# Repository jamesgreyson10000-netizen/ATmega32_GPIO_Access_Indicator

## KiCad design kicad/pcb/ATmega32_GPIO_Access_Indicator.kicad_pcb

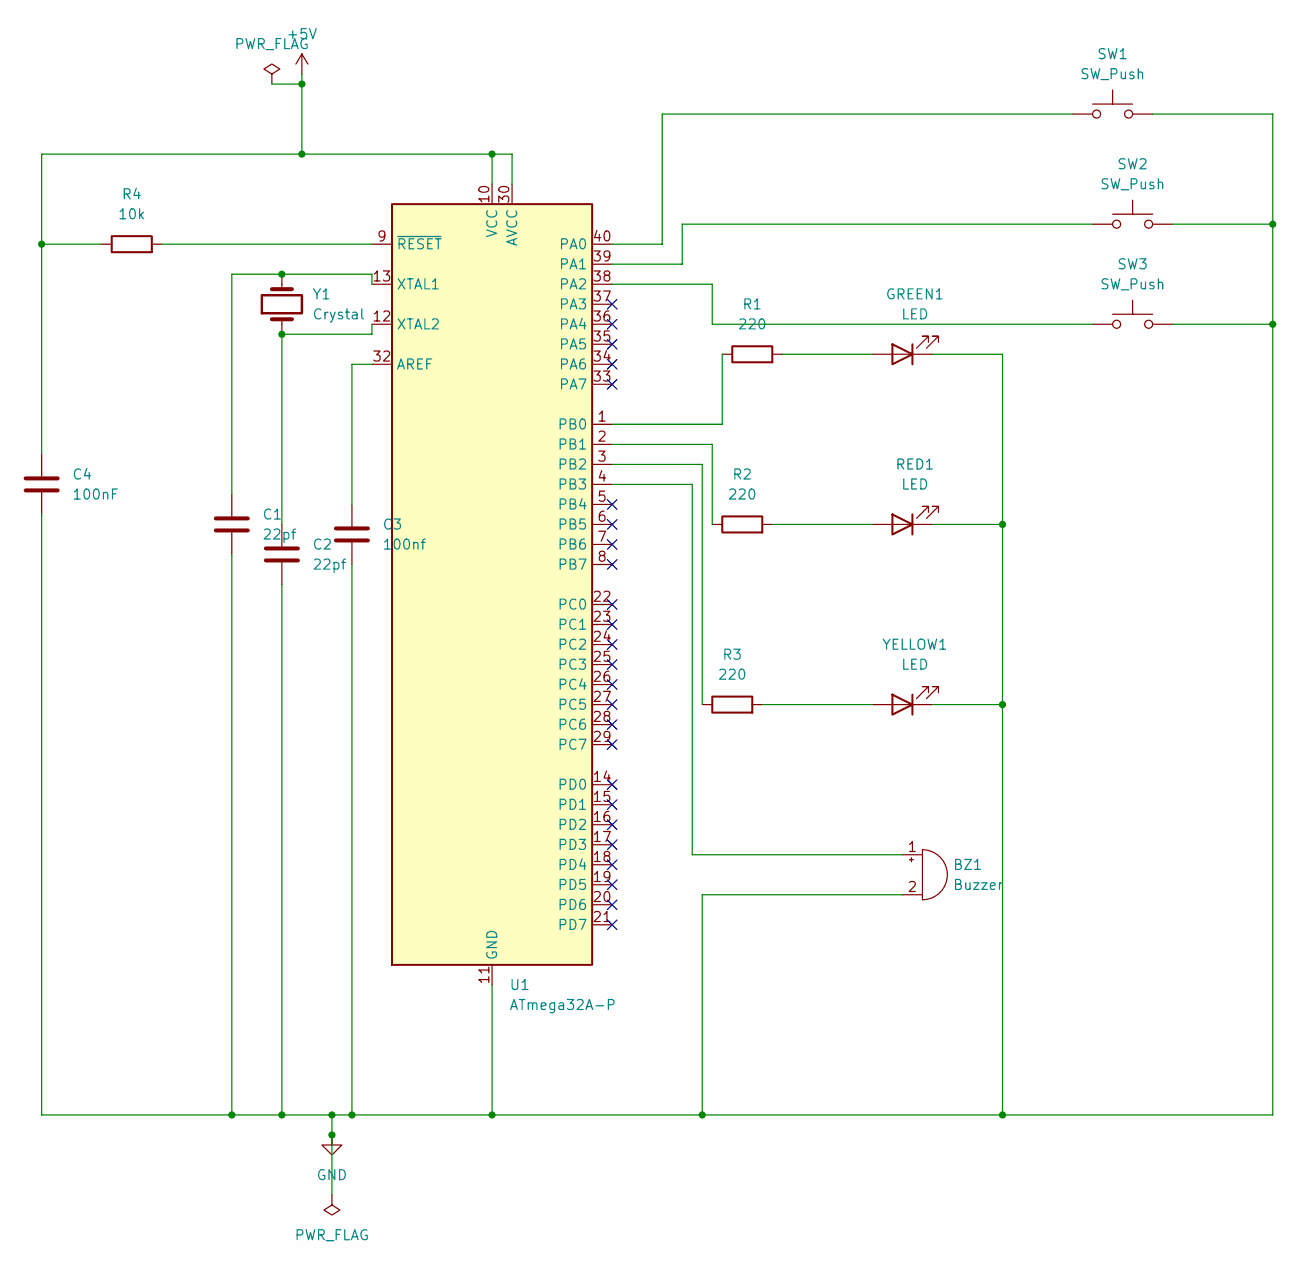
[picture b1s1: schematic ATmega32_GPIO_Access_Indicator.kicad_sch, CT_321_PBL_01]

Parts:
BZ1: Buzzer; Buzzer_12x9.5RM7.6
C1, C2: 22pf; C_Disc_D5.0mm_W2.5mm_P5.00mm
C3: 100nf; C_Disc_D5.0mm_W2.5mm_P5.00mm
C4: 100nF; C_Disc_D5.0mm_W2.5mm_P5.00mm
GREEN1: LED; LED_D5.0mm
R1, R2, R3: 220; R_Axial_DIN0207_L6.3mm_D2.5mm_P7.62mm_Horizontal
R4: 10k; R_Axial_DIN0207_L6.3mm_D2.5mm_P7.62mm_Horizontal
RED1: LED; LED_D5.0mm
SW1, SW2, SW3: SW_Push; SW_PUSH_6mm
U1: ATmega32A-P; DIP-40_W15.24mm
Y1: Crystal; Crystal_HC49-U_Vertical
YELLOW1: LED; LED_D5.0mm

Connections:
+5V: C4.1, R4.1, U1.10 (VCC), U1.30 (AVCC)
GND: BZ1.2 (-), C1.2, C2.2, C3.2, C4.2, GREEN1.1 (K), RED1.1 (K), SW1.2, SW2.2, SW3.2, U1.11 (GND), U1.31 (GND), YELLOW1.1 (K)
unnamed: BZ1.1 (+), U1.4 (PB3)
unnamed: GREEN1.2 (A), R1.2
unnamed: R2.2, RED1.2 (A)
unnamed: C3.1, U1.32 (AREF)
unnamed: SW1.1, U1.40 (PA0)
unnamed: SW2.1, U1.39 (PA1)
unnamed: SW3.1, U1.38 (PA2)
unnamed: R1.1, U1.1 (PB0)
unnamed: R2.1, U1.2 (PB1)
unnamed: R3.1, U1.3 (PB2)
unnamed: C1.1, U1.13 (XTAL1), Y1.2
unnamed: C2.1, U1.12 (XTAL2), Y1.1
unnamed: R4.2, U1.9 (~RESET)
unnamed: R3.2, YELLOW1.2 (A)

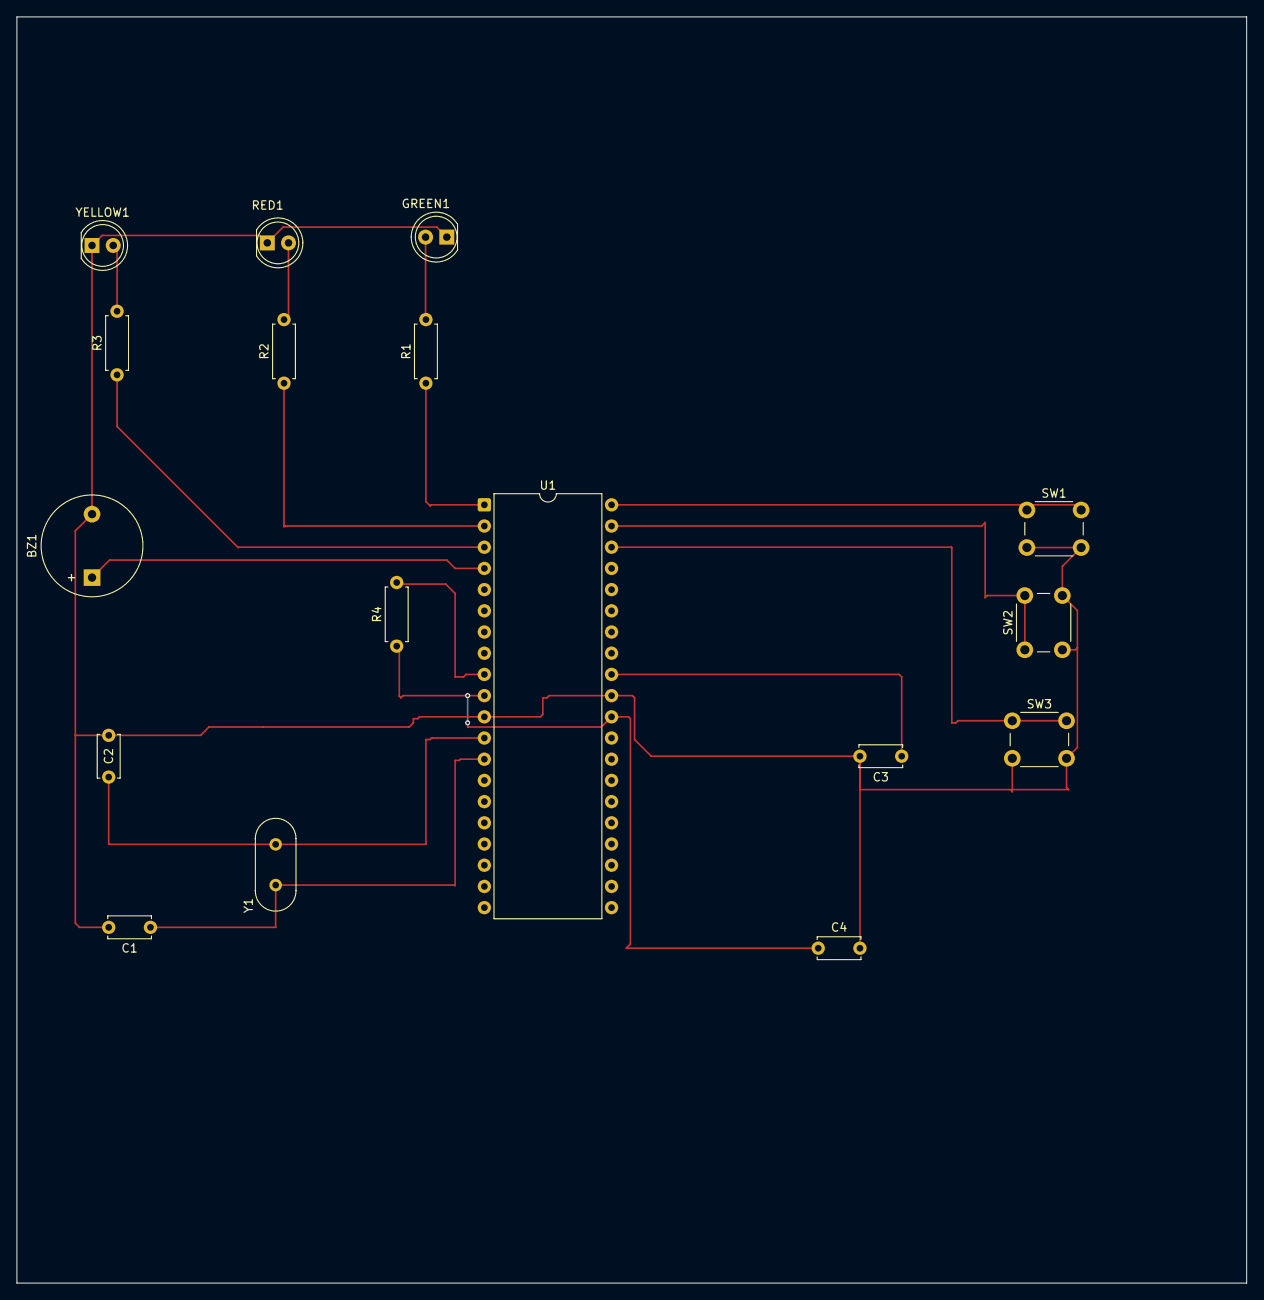
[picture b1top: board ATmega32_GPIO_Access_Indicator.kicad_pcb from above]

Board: 2 copper layers, 147.3 x 151.7 mm, 17 parts (0 on the bottom side), 16 nets.

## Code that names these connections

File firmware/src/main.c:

#define F_CPU 16000000UL
#include <avr/io.h>
#include <util/delay.h>

/* ── Pin aliases ─────────────────────────────── */
#define BTN_OK      PA0   /* Correct access button */
#define BTN_WRONG   PA1   /* Wrong access button   */
#define BTN_RESET   PA2   /* Reset button          */

#define LED_GREEN   PB0
#define LED_RED     PB1
#define LED_YELLOW  PB2
#define BUZZER      PB3

/* ── Helper macros ───────────────────────────── */
#define BTN_PRESSED(pin)   ( !(PINA & (1 << (pin))) )
#define BTN_RELEASED(pin)  (   PINA & (1 << (pin))  )

int main(void)
{
    /* PORTA = all inputs */
    DDRA  = 0x00;
    /* Enable internal pull-ups on PA0..PA2 */
    PORTA = 0xFF;

    /* PB0..PB3 = outputs */
    DDRB  = (1<<LED_GREEN) | (1<<LED_RED) | (1<<LED_YELLOW) | (1<<BUZZER);
    PORTB = 0x00;   /* all OFF */

while (1)
{
    /* Standby */
    PORTB = (1 << LED_YELLOW);

    /* Correct Access */
    if (BTN_PRESSED(BTN_OK))
    {
        PORTB = 0;

        /* Single blink and beep */
        PORTB |= (1 << LED_GREEN);
        PORTB |= (1 << BUZZER);

        _delay_ms(200);

        PORTB &= ~(1 << BUZZER);

        /* Stay active for remaining time */
        for(uint16_t i = 0; i < 3800; i += 100)
        {
            if(BTN_PRESSED(BTN_RESET))
                break;

            _delay_ms(100);
        }

        PORTB = 0;

        while(BTN_PRESSED(BTN_OK));
        _delay_ms(50);
    }

    /* Wrong Access */
    else if (BTN_PRESSED(BTN_WRONG))
    {
        PORTB = 0;

        PORTB |= (1 << LED_RED);

        /* First beep */
        PORTB |= (1 << BUZZER);
        _delay_ms(200);
        PORTB &= ~(1 << BUZZER);

        _delay_ms(200);

        /* Second beep */
        PORTB |= (1 << BUZZER);
        _delay_ms(200);
        PORTB &= ~(1 << BUZZER);

        /* Remain active for 10 seconds */
        for(uint16_t i = 0; i < 9400; i += 100)
        {
            if(BTN_PRESSED(BTN_RESET))
                break;

            _delay_ms(100);
        }

        PORTB = 0;

        while(BTN_PRESSED(BTN_WRONG));
        _delay_ms(50);
    }

    /* Reset */
    else if (BTN_PRESSED(BTN_RESET))
    {
        PORTB = 0;

        PORTB |= (1 << LED_YELLOW);

        while(BTN_PRESSED(BTN_RESET));
        _delay_ms(50);
    }
}
    return 0;
}
